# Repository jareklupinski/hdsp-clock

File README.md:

# hdsp-clock
Simple Clock Based Built Around the HDSP / PDDP type 5x7 LED Alphanumeric Display

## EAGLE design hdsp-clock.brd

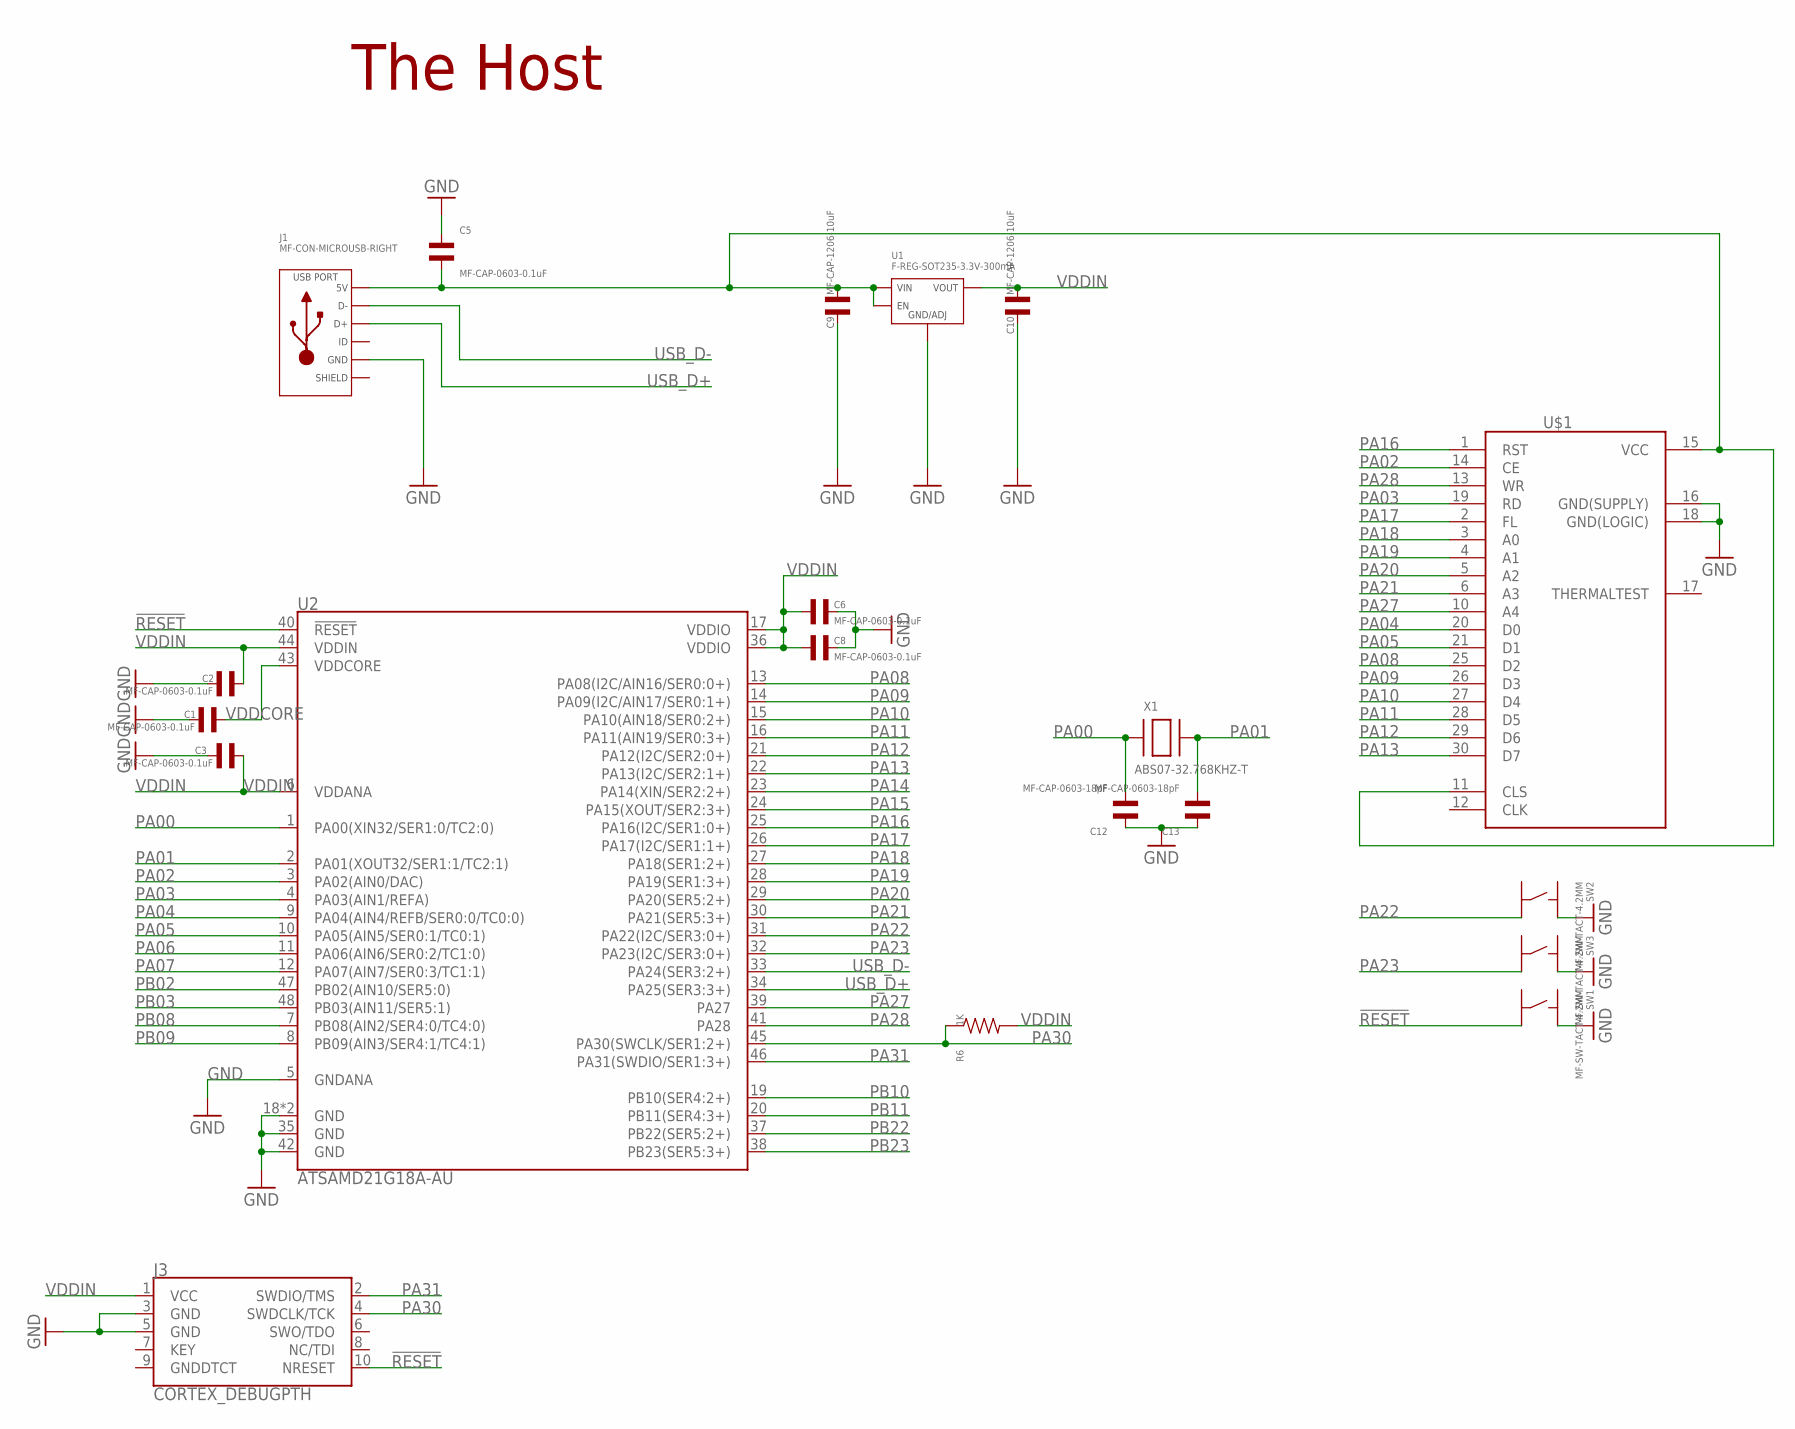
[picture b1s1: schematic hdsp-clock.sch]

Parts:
C1, C2, C3, C5, C6, C8: MF-CAP-0603-0.1uF; C0603
C9, C10: MF-CAP-1206-10uF; C1206
C12, C13: MF-CAP-0603-18pF; C0603
J1: MF-CON-MICROUSB-RIGHT; MICROUSB-RIGHT
J3: CORTEX_DEBUGPTH; 2X5-PTH-1.27MM
R6: 1K; R0603
SW1, SW2, SW3: MF-SW-TACT-4.2MM; TACT4.2MM
U1: F-REG-SOT235-3.3V-300mA; SOT-23-5
U2: ATSAMD21G18A-AU; QFN-48
U$1: HDSP-253X
X1: ABS07-32.768KHZ-T; XTAL3215

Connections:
!RESET: J3.10 (NRESET), SW1.P$4, U2.40 (!RESET!)
GND: C1.P$2, C2.P$1, C3.P$1, C5.P$1, C6.P$1, C8.P$1, C9.P$2, C10.P$2, C12.P$1, C13.P$1, J1.5 (GND), J3.3 (GND), J3.5 (GND), SW1.P$2, SW2.P$2, SW3.P$2, U1.P$2 (GND/ADJ), U1.P$4 (GND/ADJ), U2.5 (GNDANA), U2.18 (GND), U2.35 (GND), U2.42 (GND), U2.EP (GND), U$1.16 (GND(SUPPLY)), U$1.18 (GND(LOGIC))
unnamed: C5.P$2, C9.P$1, J1.1 (5V), U1.P$1 (VIN), U1.P$3 (EN), U$1.11 (CLS), U$1.15 (VCC)
PA00: C12.P$2, U2.1 (PA00(XIN32/SER1:0/TC2:0)), X1.P$1
PA01: C13.P$2, U2.2 (PA01(XOUT32/SER1:1/TC2:1)), X1.P$2
PA02: U2.3 (PA02(AIN0/DAC)), U$1.14 (CE)
PA03: U2.4 (PA03(AIN1/REFA)), U$1.19 (RD)
PA04: U2.9 (PA04(AIN4/REFB/SER0:0/TC0:0)), U$1.20 (D0)
PA05: U2.10 (PA05(AIN5/SER0:1/TC0:1)), U$1.21 (D1)
PA06: U2.11 (PA06(AIN6/SER0:2/TC1:0))
PA07: U2.12 (PA07(AIN7/SER0:3/TC1:1))
PA08: U2.13 (PA08(I2C/AIN16/SER0:0+)), U$1.25 (D2)
PA09: U2.14 (PA09(I2C/AIN17/SER0:1+)), U$1.26 (D3)
PA10: U2.15 (PA10(AIN18/SER0:2+)), U$1.27 (D4)
PA11: U2.16 (PA11(AIN19/SER0:3+)), U$1.28 (D5)
PA12: U2.21 (PA12(I2C/SER2:0+)), U$1.29 (D6)
PA13: U2.22 (PA13(I2C/SER2:1+)), U$1.30 (D7)
PA14: U2.23 (PA14(XIN/SER2:2+))
PA15: U2.24 (PA15(XOUT/SER2:3+))
PA16: U2.25 (PA16(I2C/SER1:0+)), U$1.1 (RST)
PA17: U2.26 (PA17(I2C/SER1:1+)), U$1.2 (FL)
PA18: U2.27 (PA18(SER1:2+)), U$1.3 (A0)
PA19: U2.28 (PA19(SER1:3+)), U$1.4 (A1)
PA20: U2.29 (PA20(SER5:2+)), U$1.5 (A2)
PA21: U2.30 (PA21(SER5:3+)), U$1.6 (A3)
PA22: SW2.P$4, U2.31 (PA22(I2C/SER3:0+))
PA23: SW3.P$4, U2.32 (PA23(I2C/SER3:0+))
PA27: U2.39 (PA27), U$1.10 (A4)
PA28: U2.41 (PA28), U$1.13 (WR)
PA30: J3.4 (SWDCLK/TCK), R6.P$1, U2.45 (PA30(SWCLK/SER1:2+))
PA31: J3.2 (SWDIO/TMS), U2.46 (PA31(SWDIO/SER1:3+))
PB02: U2.47 (PB02(AIN10/SER5:0))
PB03: U2.48 (PB03(AIN11/SER5:1))
PB08: U2.7 (PB08(AIN2/SER4:0/TC4:0))
PB09: U2.8 (PB09(AIN3/SER4:1/TC4:1))
PB10: U2.19 (PB10(SER4:2+))
PB11: U2.20 (PB11(SER4:3+))
PB22: U2.37 (PB22(SER5:2+))
PB23: U2.38 (PB23(SER5:3+))
SLD: J1.S1 (SLD), J1.S2 (SLD), J1.S3 (SLD), J1.S4 (SLD), J1.S5 (SLD), J1.S6 (SLD)
USB_D+: J1.3 (D+), U2.34 (PA25(SER3:3+))
USB_D-: J1.2 (D-), U2.33 (PA24(SER3:2+))
VDDCORE: C1.P$1, U2.43 (VDDCORE)
VDDIN: C2.P$2, C3.P$2, C6.P$2, C8.P$2, C10.P$1, J3.1 (VCC), R6.P$2, U1.P$5 (VOUT), U2.6 (VDDANA), U2.17 (VDDIO), U2.36 (VDDIO), U2.44 (VDDIN)

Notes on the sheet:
The Host

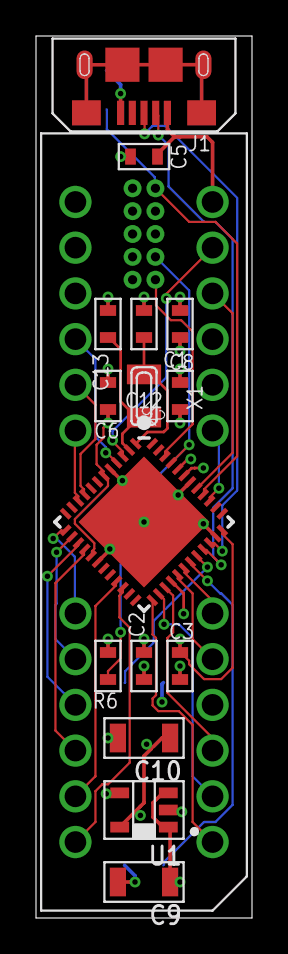
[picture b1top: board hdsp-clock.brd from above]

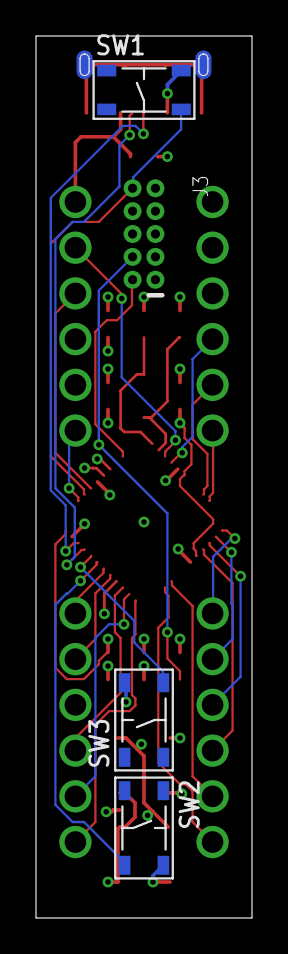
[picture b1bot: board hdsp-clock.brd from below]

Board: 4 copper layers, 12.0 x 49.0 mm, 20 parts (4 on the bottom side), 32 nets.

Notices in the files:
parts and their libraries:
SparkFun-Connectors: Licensing: Creative Commons ShareAlike 4.0 International - https://creativecommons.org/licenses/by-sa/4.0
